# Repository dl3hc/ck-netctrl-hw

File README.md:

# ck-netctrl-hw

Open-hardware daughterboard for the **SBC65EC**, usable with [**ck-netctrl**](https://github.com/dl3hc/ck-netctrl).  
Provides the hardware for controlling the automatic antenna tuner "Christian-Koppler".  
Includes the schematic and PCB, designed with [KiCad](https://www.kicad.org/).

## Contents

- Schematic files (`*.sch`)
- PCB layout (`*.kicad_pcb`)

## Requirements

- [KiCad](https://www.kicad.org/) (version ≥ 6.0 recommended)

## Usage

1. Clone the repository:
   ```bash
   git clone https://github.com/dl3hc/ck-netctrl-hw.git
2. Open the project file (*.kicad_pro) in KiCad.

3. Review the schematic and adjust the PCB if needed.

4. Generate Gerber and drill files to have the board manufactured.

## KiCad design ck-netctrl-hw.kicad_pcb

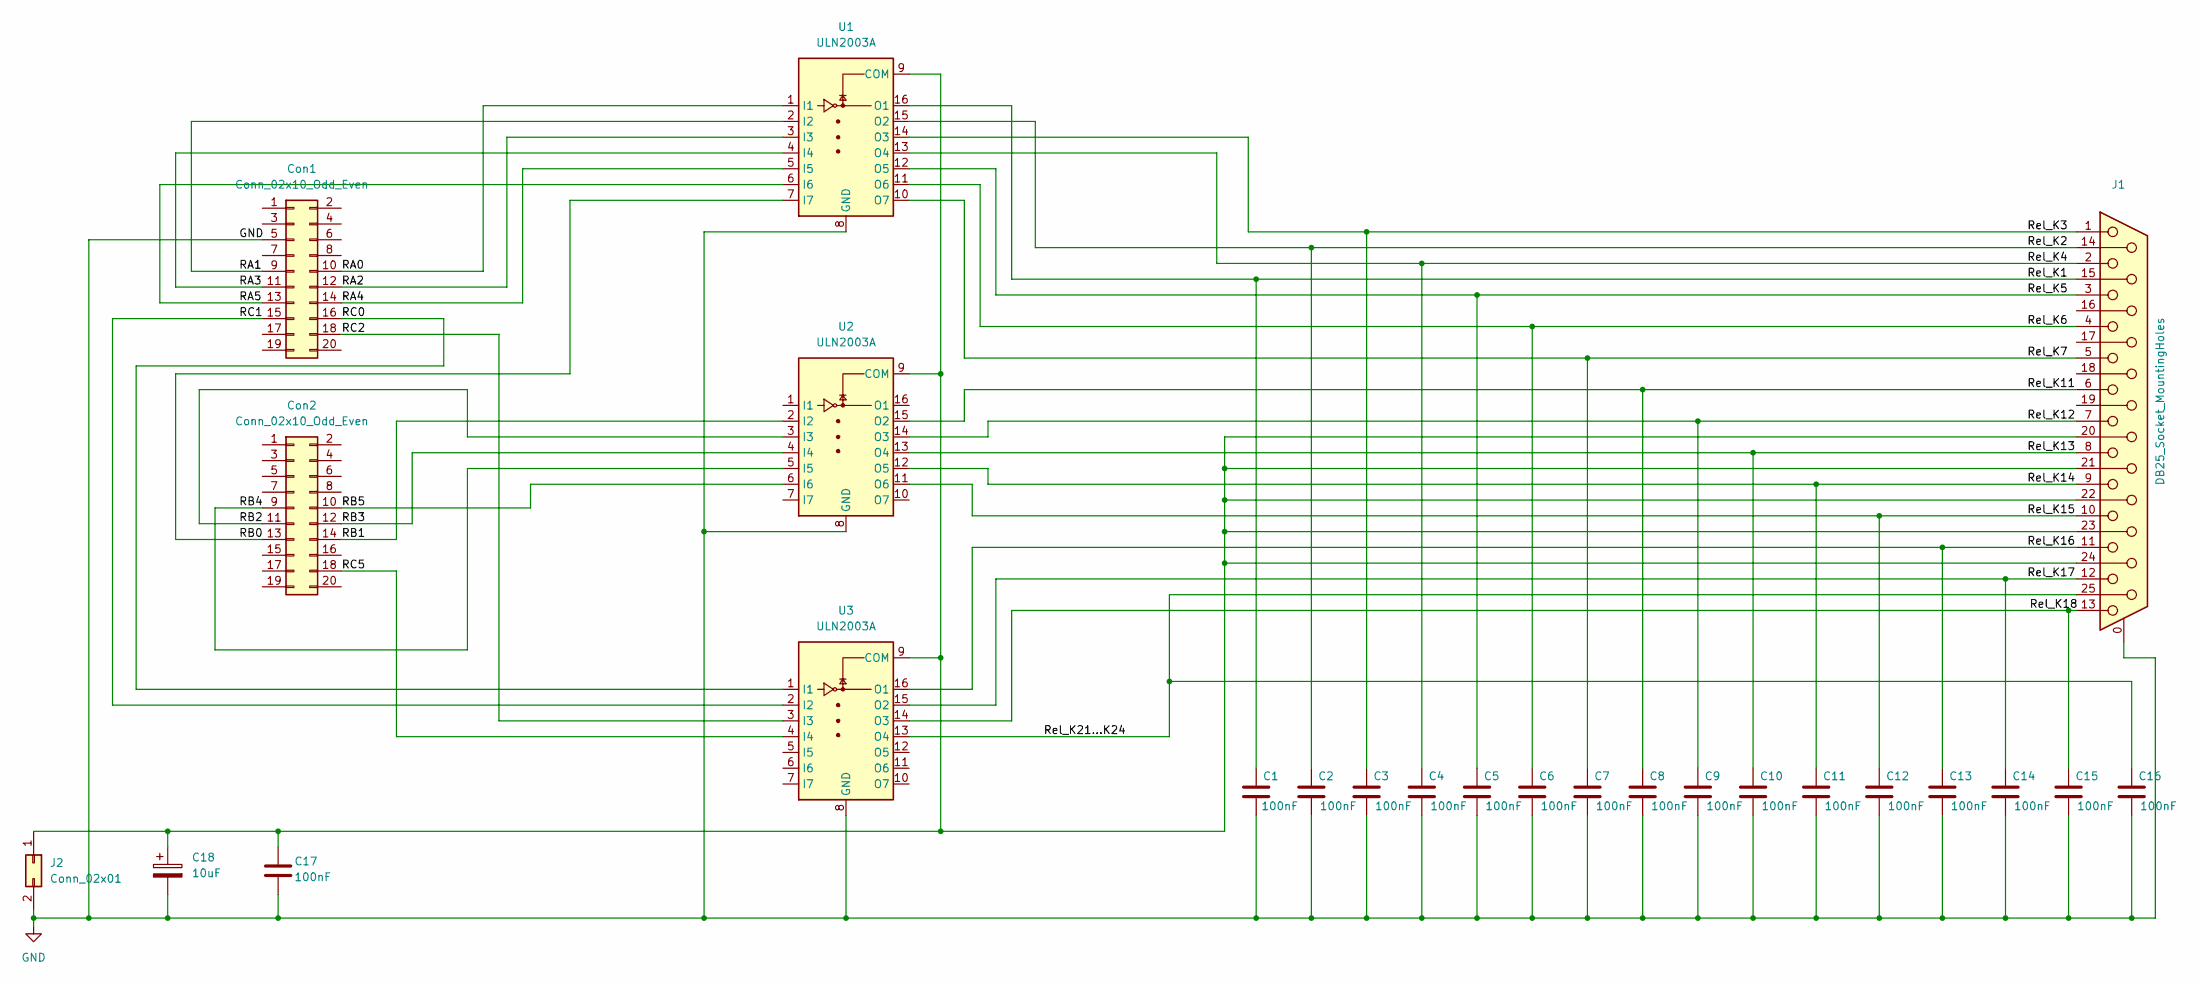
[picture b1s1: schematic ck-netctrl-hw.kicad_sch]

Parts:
C1, C2, C3, C4, C5, C6, C7, C8, C9, C10, C11, C12, C13, C14, C15, C16, C17: 100nF; C_0603_1608Metric_Pad1.08x0.95mm_HandSolder
C18: 10uF; CP_Radial_D5.0mm_P2.50mm
Con1, Con2: Conn_02x10_Odd_Even; PinHeader_2x10_P2.54mm_Vertical
J1: DB25_Socket_MountingHoles; DSUB-25_Socket_Horizontal_P2.77x2.84mm_EdgePinOffset4.94mm_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
J2: Conn_02x01; PinHeader_2x01_P2.54mm_Vertical
U1, U2, U3: ULN2003A; DIP-16_W7.62mm_LongPads

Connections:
/Rel_K1: C1.1, J1.15, U1.16 (O1)
/Rel_K2: C2.1, J1.14, U1.15 (O2)
/Rel_K3: C3.1, J1.1, U1.14 (O3)
/Rel_K4: C4.1, J1.2, U1.13 (O4)
/Rel_K5: C5.1, J1.3, U1.12 (O5)
/Rel_K6: C6.1, J1.4, U1.11 (O6)
/Rel_K7: C7.1, J1.5, U1.10 (O7)
/Rel_K11: C8.1, J1.6, U2.15 (O2)
/Rel_K12: C9.1, J1.7, U2.14 (O3)
/Rel_K13: C10.1, J1.8, U2.13 (O4)
/Rel_K14: C11.1, J1.9, U2.12 (O5)
/Rel_K15: C12.1, J1.10, U2.11 (O6)
/Rel_K16: C13.1, J1.11, U3.16 (O1)
/Rel_K17: C14.1, J1.12, U3.15 (O2)
/Rel_K18: C15.1, J1.13, U3.14 (O3)
GND: C1.2, C2.2, C3.2, C4.2, C5.2, C6.2, C7.2, C8.2, C9.2, C10.2, C11.2, C12.2, C13.2, C14.2, C15.2, C16.2, C17.2, C18.2, Con1.5, J1.0 (PAD), J2.2, U1.8 (GND), U2.8 (GND), U3.8 (GND)
unnamed: Con1.9, U1.2 (I2)
unnamed: Con1.10, U1.1 (I1)
unnamed: Con1.11, U1.4 (I4)
unnamed: Con1.12, U1.3 (I3)
unnamed: Con1.13, U1.6 (I6)
unnamed: Con1.14, U1.5 (I5)
unnamed: Con1.15, U3.2 (I2)
unnamed: Con1.16, U3.1 (I1)
unnamed: Con1.18, U3.3 (I3)
unnamed: Con2.9, U2.5 (I5)
unnamed: Con2.10, U2.6 (I6)
unnamed: Con2.11, U2.3 (I3)
unnamed: Con2.12, U2.4 (I4)
unnamed: Con2.13, U1.7 (I7)
unnamed: Con2.14, U2.2 (I2)
unnamed: Con2.18, U3.4 (I4)
unnamed: C17.1, C18.1, J1.20, J1.21, J1.22, J1.23, J1.24, J2.1, U1.9 (COM), U2.9 (COM), U3.9 (COM)
unnamed: C16.1, J1.25, U3.13 (O4)

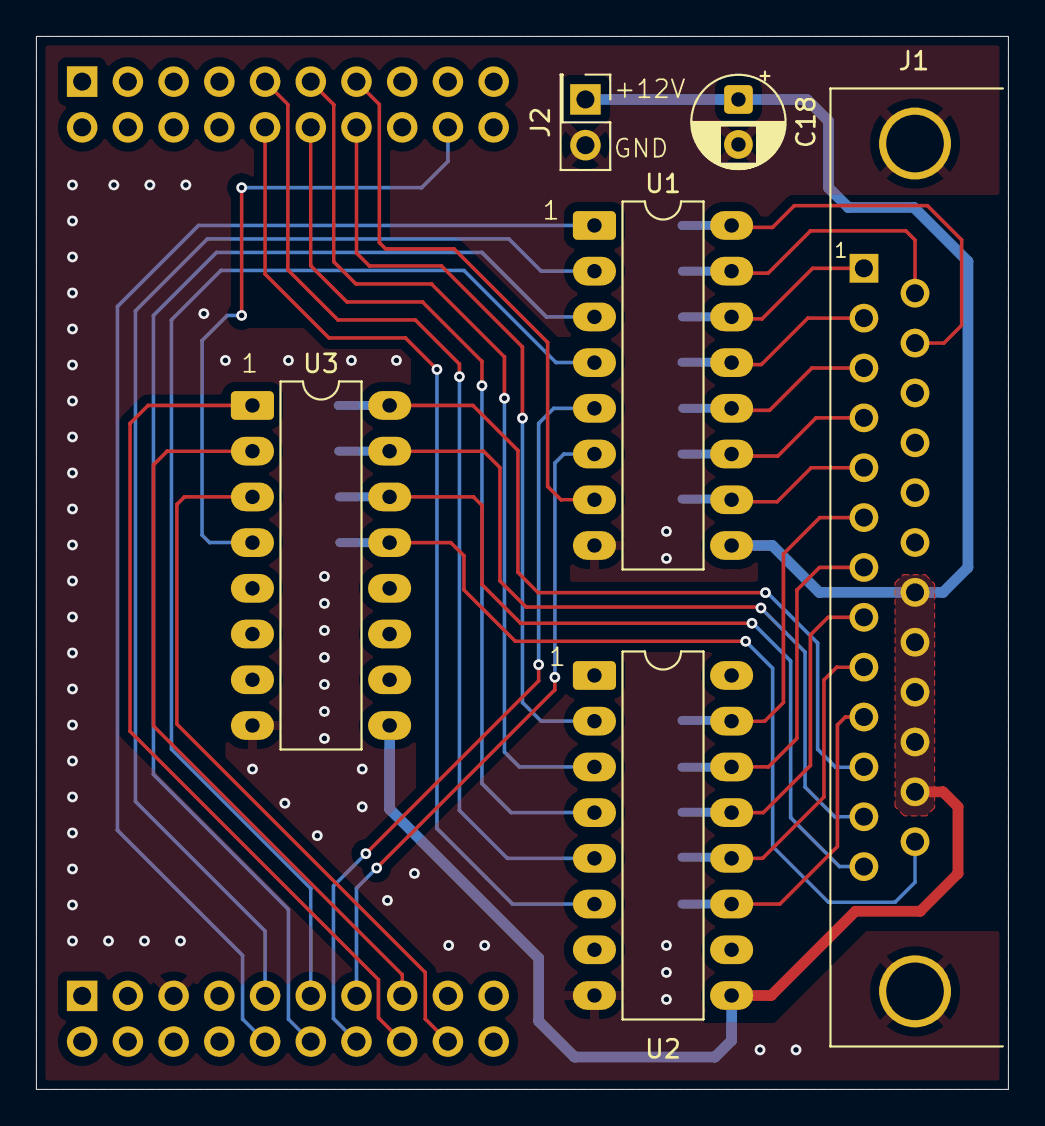
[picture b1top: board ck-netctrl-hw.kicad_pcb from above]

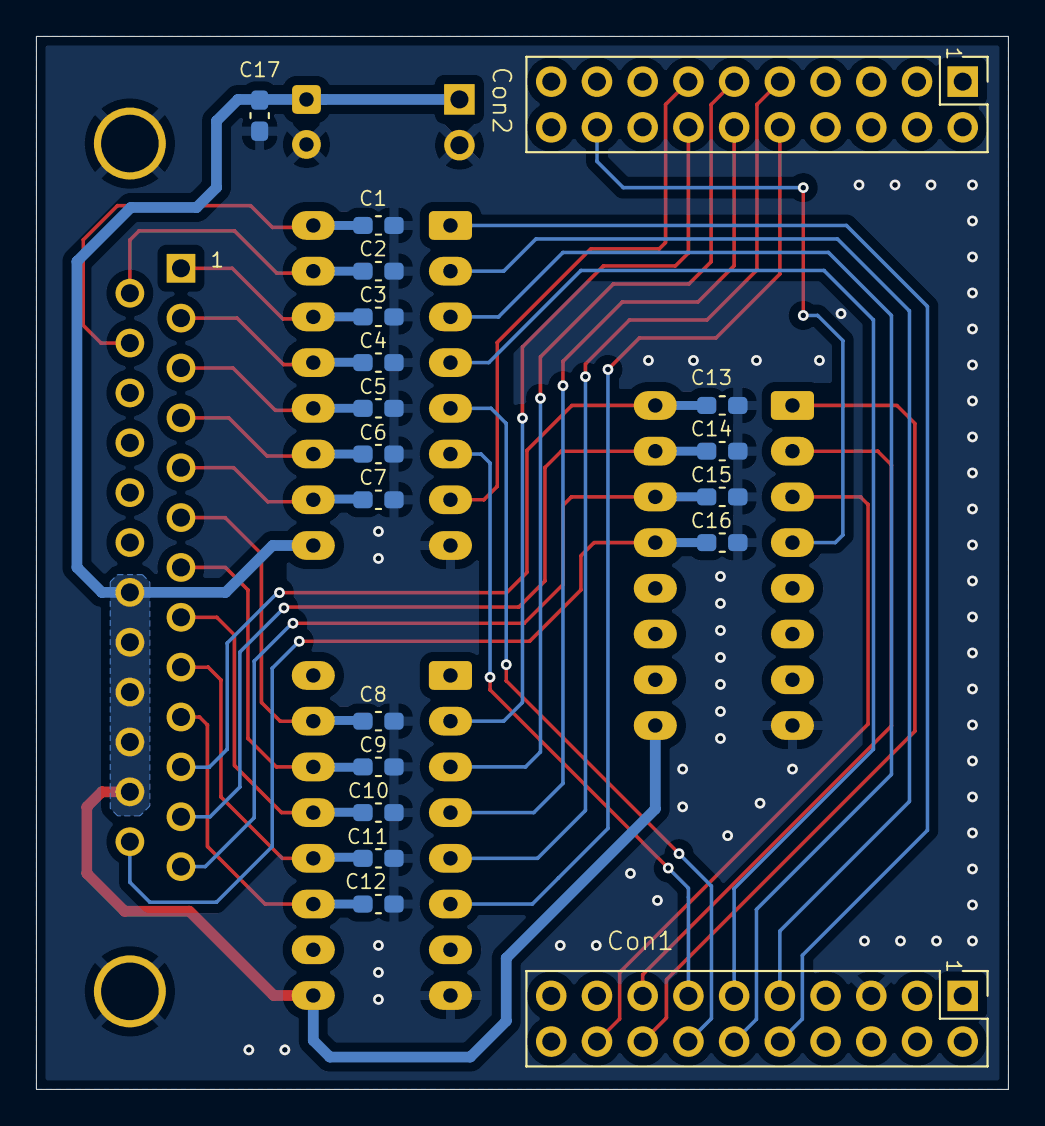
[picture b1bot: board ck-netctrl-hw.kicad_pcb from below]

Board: 2 copper layers, 54.0 x 58.5 mm, 25 parts (19 on the bottom side), 34 nets.

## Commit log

2025-09-22 add .gitignore
